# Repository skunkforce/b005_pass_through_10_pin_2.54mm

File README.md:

# edgy_board number b005
This design is part of the [edgy board project](https://github.com/skunkforce/edgy_boards). 

# getting started
This repository uses submodules. After cloning use the command 

```$ git submodule update --init --recursive```

to pull the submodules before opening the project with kicad.

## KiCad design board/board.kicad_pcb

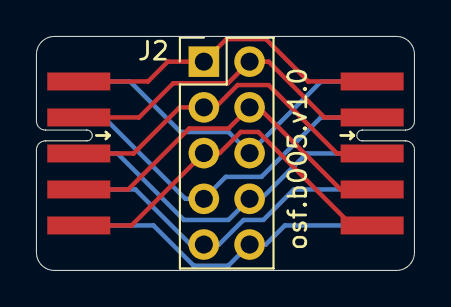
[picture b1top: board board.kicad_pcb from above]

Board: 4 copper layers, 21.0 x 13.0 mm, 3 parts (0 on the bottom side), 10 nets.

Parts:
J1: Conn_01x10_Male; on_edge_2x05_device
J2: CA2310PA10Z; PinHeader_2x05_P2.54mm_Vertical
J6: Conn_01x10_Male; on_edge_2x05_host

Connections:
unnamed: J1.1, J2.1, J6.1
unnamed: J1.2, J2.2, J6.2
unnamed: J1.3, J2.3, J6.3
unnamed: J1.4, J2.4, J6.4
unnamed: J1.5, J2.5, J6.5
unnamed: J1.6, J2.6, J6.6
unnamed: J1.7, J2.7, J6.7
unnamed: J1.8, J2.8, J6.8
unnamed: J1.9, J2.9, J6.9
unnamed: J1.10, J2.10, J6.10

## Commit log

2023-02-28 initial
